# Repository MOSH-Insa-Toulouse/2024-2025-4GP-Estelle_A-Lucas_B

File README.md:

# 2024-2025-4GP-Estelle AUBRY-Lucas BOURDARIE
Projet capteur 2024 - 2025 | Estelle AUBRY et Lucas BOURDARIE | 4ème année, 59ème promotion

# Table des matières

[Présentation du projet](https://github.com/MOSH-Insa-Toulouse/2024-2025-4GP-Haistelle-Lucbourd?tab=readme-ov-file#pr%C3%A9sentation-du-projet)

[I - Un capteur à base de graphite, c'est possible ?](https://github.com/MOSH-Insa-Toulouse/2024-2025-4GP-Haistelle-Lucbourd?tab=readme-ov-file#i---un-capteur-%C3%A0-base-de-graphite-cest-possible-)

[II - Simulation sous LTSpice](https://github.com/MOSH-Insa-Toulouse/2024-2025-4GP-Haistelle-Lucbourd?tab=readme-ov-file#ii---simulation-sous-ltspice)

[III - Réalisation du PCB avec KiCAD](https://github.com/MOSH-Insa-Toulouse/2024-2025-4GP-Haistelle-Lucbourd?tab=readme-ov-file#iii---r%C3%A9alisation-du-pcb-avec-kicad)

[IV - Le banc de test automatisé](https://github.com/MOSH-Insa-Toulouse/2024-2025-4GP-Haistelle-Lucbourd?tab=readme-ov-file#iv---le-banc-de-test-automatis%C3%A9)

[V - Le code Arduino pour piloter le projet](https://github.com/MOSH-Insa-Toulouse/2024-2025-4GP-Haistelle-Lucbourd/tree/main?tab=readme-ov-file#v---le-code-arduino-pour-piloter-le-projet)

[VI - L'application Android avec Mit App Inventor](https://github.com/MOSH-Insa-Toulouse/2024-2025-4GP-Haistelle-Lucbourd/tree/main?tab=readme-ov-file#vi---lapplication-android-avec-mit-app-inventor)

[VII - Résultats](https://github.com/MOSH-Insa-Toulouse/2024-2025-4GP-Haistelle-Lucbourd/tree/main?tab=readme-ov-file#vii---résultats)

# Présentation du projet 
 
<div align="justify"> Ce projet a été mené dans le cadre de l'UF  "Du capteur au banc de test" . L'objectif est de réaliser un capteur de déformation à base de graphite. Pour ce faire, il suffit simplement de déposer du crayon à papier sur un bout de feuille. La tension ou la compression du papier engendre une variation de résistance qui est proportionnelle à la déformation appliquée. Les principes physiques qui se cachent derrière ce phénomène sont expliqués <a href="https://github.com/MOSH-Insa-Toulouse/2024-2025-4GP-Haistelle-Lucbourd/blob/main/README.md#i---un-capteur-%C3%A0-base-de-graphite-cest-possible-">ici</a>. Le projet s'inscrit donc dans une démarche low-tech car le capteur nécessite peu de ressources et sa réalisation est accessible à tous !</div>

<div align="justify"> De plus, le capteur graphite réalisé sera testé de manière à comparer ses performances avec un capteur de déformation commercial. Nous souhaitons dégager les forces et les limites du capteur graphite par rapport à un capteur commercial. Finalement, nous établirons une conclusion quant à la possible industrialisation de ce type de capteur.</div>

<br>

<div style='display:flex' align="center">

 <p><em>Figure 1 : Banc de test complet </em></p>
</div>

<div style='display:flex' align="center">

 <p><em>Figure 2 : Mise en place des deux types de capteurs disponibles </em></p>
</div>

 ## Livrables
À la fin de ce projet, plusieurs livrables sont attendus:
- Un **PCB** sur lequel seront connectés tous les éléments cités dans la partie [Matériel utilisé](https://github.com/MOSH-Insa-Toulouse/2024-2025-4GP-Haistelle-Lucbourd/blob/main/README.md#mat%C3%A9riel-utilis%C3%A9)
- Un **banc de test** pour étudier la déformation du capteur graphite et du capteur commercial
- Un **code Arduino** qui permette de contrôler le banc de test et d'afficher les mesures de résistances
- Une <a href="https://github.com/MOSH-Insa-Toulouse/2024-2025-4GP-Haistelle-Lucbourd/blob/main/LSG180_datasheet.pdf"><strong>datasheet</strong></a> qui énonce toutes les caractéristiques du capteur graphite
- Une **application Android** (.apk) pour visualiser les relevés de mesures en direct

## Matériel utilisé 
Pour le **montage**, voici tout le matériel requis:
- Une carte Arduino UNO
- Un écran OLED (I2C) 
- Un module Bluetooth HC-05
- Un potentiomètre numérique MCP41050
- Un encodeur rotatif
- Un capteur de déformation commercial (FlexSensor) pour effectuer une comparaison
- Un <a href="https://github.com/MOSH-Insa-Toulouse/2024-2025-4GP-Haistelle-Lucbourd/blob/main/Jauge_Contrainte_A_Imprimer.pdf"><strong>capteur de déformation en papier</strong></a>
- Des crayons à papiers différents pour les tests
- Un servo moteur
- Des header de différentes tailles pour fixer les composants sur la PCB
- Une résistance de 33k

Pour réaliser **l'amplificateur transimpédance**, la liste de matériel est la suivante:
- Un amplificateur opérationnel LTC1050
- Deux condensateurs de 100nF
- Un condensateur de 1uF
- Deux résistances de 100k
- Deux résistances de 1k
- Une résistance de 10k

# I - Un capteur à base de graphite, c'est possible ?

<div align="justify">
Oui et c'est ce qu'a montré l'équipe de chercheurs Lin, CW., Zhao, Z., Kim, J. et al. dans l'article <em>Pencil Drawn Strain Gauges and Chemiresistors on Paper</em> paru en 2014. En effet, les crayons à papier sont composés de graphite et d'argile dans des proportions différentes. Par exemple, le crayon HB est constitué à 50% de graphite et à 50% d'argile. Ces différences de compositions entraînent des propriétés de conduction qui diffèrent selon le type de crayon utilisé. Lorsque l'on dépose du crayon à papier sur une feuille, les nanoparticules de graphite déposées constituent un système dit <strong>granulaire</strong>. Il s'agit d'un système dont les grains forment un réseau très désordonné au sein duquel les électrons se déplacent d'un grain à un autre par <strong>effet tunnel</strong>. L'équipe de chercheurs a donc démontré que les crayons <strong>durs</strong> comme l'HB possédaient une résistance plus importante que les crayons <strong>légers</strong> comme le 9B. Ceci s'explique par le fait que les crayons durs comme l'HB contiennent plus d'argile qu'un crayon léger qui contient plus de graphite. L'argile joue le rôle d'un isolant, plus il y en a, plus la conduction des électrons au sein du matériau est difficile. À l'inverse, les nanoparticules de graphite permettent la conduction des électrons, c'est pour cela que le crayon 9B est moins résistif que le crayon HB. 
</div>
 <br>
<div align="center">
  
  <p><em>Figure 3 : Les différents types de crayons: du 9B au 9H</em></p>
 <p><em>d'après le site Passage Clouté à l'adresse<a href="https://passagecloute.com/blog/post/8_comment-choisir-le-bon-crayon-graphite-du-9h-au-9b.html?page_type=post"> suivante</a> </em></p>
</div>
<div align="justify">
De plus, les chercheurs ont aussi prouvé que les crayons pouvaient se comporter comme des <strong>jauges de contraintes</strong>. En dessinant au crayon une forme de U avec deux rectangles au bout pour les électrodes de contact, les chercheurs ont remarqué qu'une déformation en compression et en tension avaient des effets différents sur la <strong>résistance</strong> du capteur. La compression du capteur compresse les particules de graphite et induit une diminution de la résistance. Au contraire, la tension du capteur éloigne les particules de graphite ce qui augmente résistance. 
</div>
<div align="center">
  
  <p><em>Figure 4 : Structure granulaire en compression et en tension</em></p>
</div>

<div align="center">
  
  <p><em>Figure 5 : c) Capteur graphite en compression d) Capteur graphite en tension </em></p>
 <p><em>d'après Lin, CW., Zhao, Z., Kim, J. et al., 2014 </em></p>
</div>

<div align="justify">
Cependant, l'équipe conclut que l'observation de ces phénomènes n'est pas possible pour des crayons composés de plus d'argile que le crayon HB. Selon eux, le réseau de nanoparticules du crayon HB se situe juste au dessus du <strong>seuil de percolation</strong>. Le seuil de percolation est le seuil à partir duquel le matériau devient conducteur car les électrons peuvent traverser. Néanmoins, nous allons montrer que, grâce à l'utilisation d'un <strong>amplificateur transimpédance</strong>, il est possible de mesurer des résistances pour des crayons plus durs que le HB. Par conséquent, la structure de ces crayons permet le passage des électrons et ne se situe pas en dessous du seuil de percolation.   
</div>

# II - Simulation sous LTSpice et formules utiles

<div align="justify"> D'après l'étude menée par les chercheurs, le capteur graphite a une résistance qui peut varier d'une centaine de kohms à quelques Mohms. Les résistances très élevées sont délicates à mesurer. En effet, une méthode classique consiste à utiliser un ohmmètre mais pour mesurer des résistances de cet ordre de grandeur les options sont chères. De plus, nous utilisons une carte Arduino dont l'impédance maximale de la source ne peut pas dépasser 10 kohms. Il n'est donc pas possible de brancher directement notre capteur graphite sur la carte. De ce fait, nous allons amplifier le signal et diminuer son impédance à l'aide d'un amplificateur transimpédance. Nous utilisons pour cela un amplificateur opérationnel LTC1050 car il est suffisamment sensible pour amplifier correctement le signal. Il s'agit également d'un amplificateur très précis, qui possède un offset voltage de 5 uV, négligeable par rapport à la tension mesurée sur l'entrée non-inverseuse. Si l'on considère que le courant délivré par le capteur graphite est de 100 nA et que la résistance de R1 vaut 100komhs, alors la tension Vep = I x R1 = 10 mV >> 5 uV.</div>

## A) Montage avec l'amplificateur transimpédance

<div align="center">
  
  <p><em>Figure 6 : Schéma de l'amplificateur transimpédance dans LTSpice </em></p>
</div>
<div align="justify">
De plus, il va falloir filtrer le bruit. Pour ce faire, nous mettons en place 3 filtres passe-bas:
 <ul>
  <li>un pour filtrer le bruit du capteur en jaune.</li>
  <li>un pour filtrer le bruit à 50Hz en vert.</li>
  <li>un pour filtrer les variations plus rapides que 7kHz en rouge. D'après le critère de Shannon, fech > 2*fsignal. Or, pour une carte Arduino, la fréquence d'échantillonnage vaut 15 kHz donc fsignal < 7kHz.  </li>
</ul>
</div>

## B) Formules
À partir de ce montage, nous pouvons établir la formule nécessaire pour relier la tension en sortie de l'amplificateur transimpédance à la résistance du capteur graphite.

<div align="center">
  
  <p><em>Equation 1 : Formule qui lie la résistance du capteur graphite à la tension Vadc mesurée en sortie </em></p>
</div>

De la même manière, pour le capteur commercial, nous faisons un pont diviseur de tension avec une résistance de 33k. La formule qui relie la tension de sortie à la résistance du capteur commercial est la suivante: 

<div align="center">
  
  <p><em>Equation 2 : Formule qui lie la résistance du capteur commercial à la tension V_flex mesurée en sortie </em></p>
</div>

# III - Réalisation du PCB avec KiCAD

<div align="justify"> Ensuite, nous avons dessiné un PCB simple face à l'aide du logiciel KiCAD. Il est à noter que l'entrée du capteur graphite est reliée à l'amplificateur transimpédance. Afin de permettre un meilleur contrôle de l'amplification du signal, la résistance R2 de la figure 7 a été remplacée par un potentiomètre numérique. Le conditionneur utilisé pour le capteur commercial est un pont diviseur de tension avec une résistance de 33k. De plus, nous avons ajouté un condensateur pour faire du débouncing sur l'encodeur rotatif. Nous avons suivi ces étapes:</div>

**1)** **Dessiner** les composants tels que l'OLED, l'encodeur rotatif, le module Bluetooth, le capteur commercial et le capteur graphite

**2)** Réaliser les **empreintes** de ces composants

**3)** Sélectionner les résistances, les condensateurs et l'AOP pour **réaliser l'amplificateur transimpédance** dans l'éditeur de Schématique

**4)** Établir les **points de connexion** entre la carte Arduino et tous les composants

**5)** **Positionner** les composants sur la PCB

**6)** Importer les **modèles 3D** pour les composants non-présents par défaut dans les librairies (OLED, encoder rotatif, module Bluetooth, capteur commercial)

**7)** Faire **le routage** dans l'éditeur de PCB en évitant au maximum les masses flottantes et les vias

**N.B**: Le servo moteur n'apparaît pas ici car il sera relié à la carte Arduino par le biais d'un header.
<div align="center">
  
  <p><em>Figure 7 : Vue depuis l'éditeur de Schématique </em></p>
</div>

<div align="center">
  
  <p><em>Figure 8 : Vue depuis l'éditeur de PCB </em></p>
</div>

<div align="center">
  
  <p><em>Figure 9 : Vue 3D </em></p>
</div>

# IV - Le banc de test automatisé

<div align="center">
  
  <p><em>Figure 10 : Rendu du banc de test final</em></p>
</div>

<div align="justify"> Afin d'optimiser notre relevé de mesures, nous avons mis au point un banc de test qui courbe automatiquement le capteur de déformation. De cette manière, nous minimisons les risques de dégradation du capteur graphite lors des relevés de mesure car nous ne touchons pas le capteur dès lors qu'il est positionné sur le banc de test. Le banc de test a été réalisé sous Fusion360 puis imprimé en 3D. Ce dernier permet des relevés entièrement personnalisables par l'utilisateur grâce au code Arduino développé. Avec ce banc de test, il est possible de réaliser des mesures sur le capteur graphite et le capteur commercial. Les mesures en tension se sont révélées être plus faciles à mettre en place que les mesures en compression, qui sont plus délicates.</div>

## A) La glissière pilotée par le servo moteur

<div align="center">
  
  <p><em>Figure 11 : Rendu de la glissière écrantée avec encoche fendue ainsi que de l'engrenage fixé au servo</em></p>
</div>

<div align="justify">  Pour courber le capteur de déformation, nous avons utilisé un système de glissière qui se déplace sous l'action du servo moteur. En effet, nous avons conçu un engrenage qui se fixe sur le servo moteur et dont la rotation entraîne une glissière crantée. Le bout de cette glissière est fait en forme d'encoche pour maintenir le capteur. Pour éviter que le capteur sorte de l'encoche au cours des mesures, nous avons également imprimé des petites cales qui assurent le bon positionnement du capteur. Enfin, nous avons imprimé deux glissières différentes, une pour le capteur commercial et une pour le capteur graphite car le capteur commercial est plus long que le capteur graphite. La glissière du capteur commercial possède une petite fente en bas de l'encoche (voir figure 11) pour le maintenir correctement et permettre une déformation qui épouse au mieux les rayons de courbure.</div>

## B) Les rayons de courbure interchangeables
<div style='display:flex' align="center">

 <p><em>Figure 12 : Gamme de rayons de courbure imprimés en 3D</em></p>
</div>

<div align="justify"> Pour tester les capteurs, nous avons imprimé huit supports en 3D avec différents rayons de courbure. Ces supports s'imbriquent sur le banc de test comme nous pouvons le voir sur la figure 11. Les numéros qui figurent sur les supports correspondent à l'angle entre le bord jaune et le bord rouge indiqués sur la figure 12. 
</div>

# V - Le code Arduino pour piloter le projet

## A) Description générale 

<div align="justify"> Le code développé permet à l'utilisateur de gérer facilement et intuitivement le banc de test pour effectuer les mesures. L'affichage se fait sur l'écran OLED sur lequel apparaissent <a href="https://github.com/MOSH-Insa-Toulouse/2024-2025-4GP-Haistelle-Lucbourd/tree/main?tab=readme-ov-file#b-les-diff%C3%A9rentes-fonctionalit%C3%A9s">les différentes fonctionnalités</a>. L'utilisateur peut parcourir les différents menus en tournant l'encoder rotatif dans le sens horaire ou anti-horaire. Pour "rentrer" dans un menu, il suffit d'appuyer sur l'encoder et l'interface se met à jour. Chaque menu possède sa propre fonctionnalité que l'utilisateur peut librement régler. En principe, l'ordre des menus correspond à l'ordre dans lequel l'utilisateur doit effectuer les réglages avant de lancer la mesure via le menu "Démarrage" à la fin. Il est préférable de ne pas placer le capteur sur le banc de test avant le menu "Borne" pour ne pas l'abîmer lors des précédents réglages.</div>

## B) Les différentes fonctionnalités
### 1 - Le menu "BIENVENUE"
<div align="center">
   
 <p><em>Figure 13 : menu de bienvenue </em></p>
</div>
Ce menu souhaite la bienvenue à l'utilisateur. Il ne possède pas de fonctionnalité particulière.

### 2 - Le menu "CONFIGURATION"
<div style='display:flex' align="center">

 <p><em>Figure 14 : menu de configuration </em></p>
</div>
<div align="justify"> Ce menu permet à l'utilisateur de définir quel type de capteur il utilise entre le capteur graphite et le capteur commercial. Une fois le type de capteur sélectionné (fond bleu et écriture noire), il suffit d'appuyer sur l'encoder rotatif pour enregistrer le choix. </div>

### 3 - Le menu "CALIBRATION"
 <div style='display:flex' align="center">

 <p><em>Figure 15 : menu de calibration </em></p>
</div>
<div align="justify"> Dans ce menu, l'utilisateur peut régler la valeur prise par le potentiomètre numérique de manière à ne pas saturer l'amplificateur opérationnel. Attention, ce menu n'est utile que lorsque le type de capteur choisi est le graphite car le potentiomètre numérique est utilisé dans l'amplificateur transimpédance. L'interface affiche à la fois la valeur de résistance prise par le potentiomètre numérique et le signal lu par l'entrée analogique du capteur graphite. Il s'agit donc d'une valeur comprise entre 0 et 1023. Lors des mesures, il faut également anticiper la variation de résistance engendrée par la déformation du capteur graphite. En effet, en compression, la résistance lue diminue donc le signal augmente et peut, si le potentiomètre n'est pas correctement réglé, saturer l'AOP. </div>

### 4 - Le menu "VITESSE"
<div style='display:flex' align="center">

 <p><em>Figure 16 : menu de réglage de la vitesse </em></p>
</div>
<div align="justify"> Dans le menu "Vitesse", l'utilisateur peut régler la vitesse à laquelle il souhaite effectuer les mesures, c'est-à-dire, la vitesse à laquelle la glissière reliée au servo moteur va se déplacer. L'écran affiche un pourcentage qui correspond à la vitesse du servo moteur. 0% correspond à la <strong>vitesse minimale</strong> et 100% la <strong>vitesse maximale</strong>. Pour augmenter la vitesse, il est nécessaire de tourner l'encodeur rotatif dans le sens <strong>anti-horaire</strong> car il s'agit en réalité de <strong>diminuer</strong> le délai entre chaque incrément du servo moteur. La vitesse maximale correspond à un délai de <strong>5ms</strong> tandis que la vitesse minimale correspond à un délai de <strong>40ms</strong>. De plus, lorsque la vitesse change (= l'encodeur change de position), le servo moteur effectue un aller-retour au cours duquel il est possible faire varier la vitesse du servo à l'aide de l'encodeur jusqu'à obtenir la vitesse désirée. L'affichage en % de la vitesse s'effectue <strong> à la fin </strong>  de l'aller-retour. Il n'y a donc pas d'affichage en direct de la vitesse mais seulement après que le servo moteur ait fait un aller-retour. D'après la figure 17 ci-dessous, comme l'encodeur est utilisé pour faire varier le délai, la variable encoder_pos peut prendre des valeurs comprises entre 5 et 40 uniquement. </div>
<div align="center">
  
  <p><em>Figure 17 : Algorigramme qui présente le déroulé de la fonction "Vitesse"</em></p>
</div>

### 5 - Le menu "BORNE"
<div style='display:flex' align="center">

 <p><em>Figure 18 : menu de réglage de la borne </em></p>
</div>
<div align="justify"> À partir de cette étape, il faut placer le capteur sur le banc de test. Le menu "Borne" permet à l'utilisateur de régler la position maximale du servo moteur et par conséquent, celle de l'encoche qui maintient le capteur contre le support. De cette manière, l'utilisateur peut s'assurer que le capteur épouse correctement la forme du rayon de courbure. Pour augmenter ou diminuer la position maximale, il faut tourner l'encodeur rotatif dans le sens horaire ou anti-horaire. </div>
 
### 6 - Le menu "MODE de MESURE"
<div style='display:flex' align="center">

 <p><em>Figure 19 : menu de sélection du mode de mesure </em></p>
</div>
<div align="justify"> À l'intérieur de ce menu, l'utilisateur définit le nombre de mesures qu'il souhaite faire. En effet, nous avons pensé que comme les valeurs de résistances lues en direct peuvent parfois varier, il pourrait être intéressant de permettre à l'utilisateur de faire une moyenne sur un nombre de mesures qu'il définit. De ce fait, lorsque la valeur choisie est "5" par exemple, le code effectuera 5 relevés de résistances pour un même rayon de courbure. Le servo fera donc un aller, une mesure puis un retour, le tout 5 fois. La valeur finale affichée correspondra à une moyenne de la résistance sur les 5 mesures. Le nombre de mesure réalisable est compris entre 1 et 20. </div>

### 7 - Le menu "DÉMARRAGE"
<div style='display:flex' align="center">

 <p><em>Figure 20 : menu de démarrage de la mesure </em></p>
</div>
Le menu "Démarrage" permet de lancer l'acquisition de mesure. Il prend en compte tous les paramètres précédemment définis par l'utilisateur. Par exemple pour des paramètres tels que:
<ul>
<li><strong>Vitesse</strong>: 52%</li>
<li><strong>Borne</strong>: 150</li>
<li><strong>Mode de mesure</strong>: 5</li>
Le servo moteur effectuera 5 aller-retours jusqu'à la position 150 du servo à une vitesse de 52% de la vitesse maximale.
</ul>
<div align="center">
  
  <p><em>Figure 21 : Algorigramme qui présente le déroulé de la fonction "Démarrage"</em></p>
</div>

### 8 - Le menu "LiveVIEW"
<div style='display:flex' align="center">

 <p><em>Figure 22 : menu de mesure en direct </em></p>
</div>
<div align="justify"> Ce menu permet un affichage en direct de la valeur de résistance lue par l'entrée analogique. Il faut se placer à l'intérieur de ce menu pour utiliser l'application Android car les données sont envoyées au téléphone via le module Bluetooth HC-05. </div>

# VI - L'application Android avec Mit App Inventor

<div align="justify"> Cette application permet de recevoir les données envoyées par le module Bluetooth du PCB et de les afficher sous forme de graphique.

[insérer image explicative]

## A) L'écran de démarrage
<div align="justify"> L'écran de démarrage comporte un seul bouton "Démarrer" sur lequel il suffit de cliquer pour lancer l'application.</div>
<br>
<div align="center">
  
  <p><em>Figure 23 : Écran de démarrage de l'application </em></p>
</div>

## B) L'interface principale et ses fonctionnalités

<div align="justify"> Sur le deuxième écran, l'utilisateur doit tout d'abord connecter son téléphone au module Bluetooth pour recevoir les données. Lorsque la connexion est établie, le bouton "Bluetooth connexion" s'affiche en vert. Ensuite, un switch permet de définir quel capteur est utilisé. Si l'on utilise le capteur graphite, il faut renseigner la valeur du potentiomètre numérique dans la case rose pour afficher la bonne valeur de résistance dans la case bleu clair. Par défaut, la valeur de R2 vaut 875 ohms. Un graphique en dessous permet d'afficher en direct les bytes reçus par le module Bluetooth. Les bytes reçus sont également affichés dans la case jaune en dessous du graphique. </div>
<br>
<div align="center">
  
  <p><em>Figure 24 : Écran pour le relevé de mesures en direct </em></p>
</div>

# VII - Résultats

<div align="justify"> 
Pour réaliser nos mesures, nous avons tracé l'évolution de la variation relative de résistance en fonction de la déformation. Pour la variation relative de résistance, nous appliquons la formule ci-dessous. Rplat correspond à la résistance du capteur graphite sans déformation appliquée et Rcourbé à la résistance mesurée quand le capteur est déformé.
<div align="center">
  
  <p><em>Equation 3 : Formule de la variation relative de résistance</em></p>
</div>
Pour calculer la déformation, nous effectuons le calcul ci-dessous pour tous nos rayons de courbure afin de trouver la déformation correspondante. e correspond à l'épaisseur de la feuille de papier utilisée.
 <div align="center">
  
  <p><em>Equation 4: Formule pour calculer la déformation</em></p>
</div>
Le coefficient de proportionnalité qui lie la variation relative de résistance et la déformation correspond à la <strong>sensibilité</strong> du capteur. 
</div>

<div align="justify">  Pour réaliser tous nos tests nous avons choisi une vitesse de 52% pour le servo moteur. Les crayons testés sont le 6B, 5B, 4B, 3B, B, HB, F et H pour des mesures en tension. Les tests ont été effectués sur chaque rayon de courbure disponible. Pour les mesures en compression, les tests ont été réalisés sur les crayons 6B, 3B et HB pour des rayons de courbure allant jusqu'à 24 mm. Pour <strong> chaque point </strong>, nous avons réalisé 5 mesures de résistance pour un type de crayon et un rayon de courbure donné et pris la moyenne de ces 5 mesures comme résultat final. Au total, pour les mesures en tension cela nous fait 8 (crayons) x 8 (supports) x 5 (mesures pour 1 type de crayon et un rayon de courbure donné) = <strong>320 mesures</strong>. Pour les mesures en compression, nous avons 3 (crayons) x 6 (supports) x 5 (mesures) = <strong>90 mesures</strong>. Nous n'avons pas pu réaliser les mesures en compression pour tous les rayons de courbure disponibles car le capteur se détériorait au fur et à mesure des tests.  Ainsi, pour ce projet nous avons effectué plus de <strong>400</strong> mesures pour caractériser nos capteurs. 
</div>

## A) Les mesures obtenues

<div align="justify"> Voici les résultats de toutes nos mesures en tension (figure 25) et en compression (figure 26). Les courbes obtenues sont cohérentes avec les résultats de Lin, CW., Zhao, Z., Kim, J. et al. En effet, les crayons plus durs comme le 6B possèdent une sensibilité plus faible que les crayons plus légers comme le HB par exemple. Voici le graphique qui regroupe nos résultats pour une déformation en tension.   </div>

<div align="center">
  
  <p><em>Figure 25 : Résultats de la déformation du capteur graphite en tension pour différents crayons</em></p>
</div>

Voici le graphique qui regroupe nos résultats pour une déformation en compression.

<div align="center">
  
  <p><em>Figure 26 : Résultats de la déformation du capteur graphite en compression pour différents crayons</em></p>
</div>

Voici quelques courbes individuelles qui permettent d'apprécier l'évolution linéaire de la variation relative de résistance en fonction de la déformation appliquée.

<div align="center">
  
  <p><em>Figure 27 : tension du crayon 3B</em></p>
</div>

<div align="center">
  
  <p><em>Figure 28 : tension du crayon HB </em></p>
</div>

<div align="center">
  
  <p><em>Figure 29 : tension du crayon H </em></p>
</div>

<div align="center">
  
  <p><em>Figure 30 : compression du crayon 3B </em></p>
</div>

<div align="center">
  
  <p><em>Figure 31 : compression du crayon HB </em></p>
</div>

Nous avons également réalisé nos tests sur le capteur commercial pour pouvoir effectuer une comparaison.

<div align="center">
  
  <p><em>Figure 32 : tension du capteur commercial </em></p>
</div>

Voici un tableau récapitulatif de nos relevés de mesures.

<div align="center">
  
  <p><em>Figure 33 : Sensibilité des capteurs testés </em></p>
</div>

## B) Comparaison avec un capteur commercial: qui sera le meilleur ?
<div align="justify">   Grâce aux résultats ci-dessus, nous pouvons comparer les performances du capteur graphite par rapport au capteur commercial. Ce sont deux capteurs différents qui ont chacun leur propre domaine d'utilisation. Voici les points positifs et négatifs du capteur commercial.
</div>
<br>
 
<div align="center">
<table>
  <thead>
    <tr>
      <th>Points positifs</th>
      <th>Points négatifs</th>
    </tr>
  </thead>
  <tbody>
    <tr>
      <td>Précision importante</td>
      <td>Impossible de faire une mesure en compression</td>
    </tr>
    <tr>
      <td>Sensibilité élevée</td>
      <td>Coûte beaucoup plus cher qu'un capteur graphite (10 euros environ)</td>
    </tr>
   <tr>
      <td>Réutilisable un grand nombre de fois sans détérioration</td>
      <td></td>
    </tr>
  </tbody>
</table>
</div>
 
 De même, voici un tableau qui récapitule les avantages et inconvénients du capteur graphite.
 
 <div align="center">
<table>
  <thead>
    <tr>
      <th>Points positifs</th>
      <th>Points négatifs</th>
    </tr>
  </thead>
  <tbody>
    <tr>
      <td>Sensibilité qui peut rivaliser avec celle du capteur commercial selon le type de crayon utilisé</td>
      <td>Manipulation délicate car le capteur se détériore au moindre contact</td>
    </tr>
    <tr>
      <td>Permet de réaliser des mesures en compression</td>
      <td>Si le capteur est courbé trop de fois les fibres du papiers se cassent ce qui nuit à la mesure</td>
    </tr>
  </tbody>
</table>
</div>

<div align="justify"> Pour conclure, le capteur graphite a une gamme d'utilisation plus large que le capteur commercial. Sa sensibilité peut égaler celle du capteur commercial. Il reste cependant très délicat et contraignant à manipuler. Nous pensons qu'une piste d'amélioration possible pour ce capteur serait d'envisager un moyen de l'encapsuler pour protéger le graphite. Avec une telle solution, il serait possible de l'industrialiser pour le rendre plus durable. Toutefois, la solution ne devra pas être trop coûteuse pour ne pas perdre l'intérêt de ce capteur qui se veut low-tech avant tout.
</div>

# Contacts

Estelle AUBRY:<a> eaubry@insa-toulouse.fr</a>

Lucas BOURDARIE:<a> bourdari@insa-toulouse.fr</a>

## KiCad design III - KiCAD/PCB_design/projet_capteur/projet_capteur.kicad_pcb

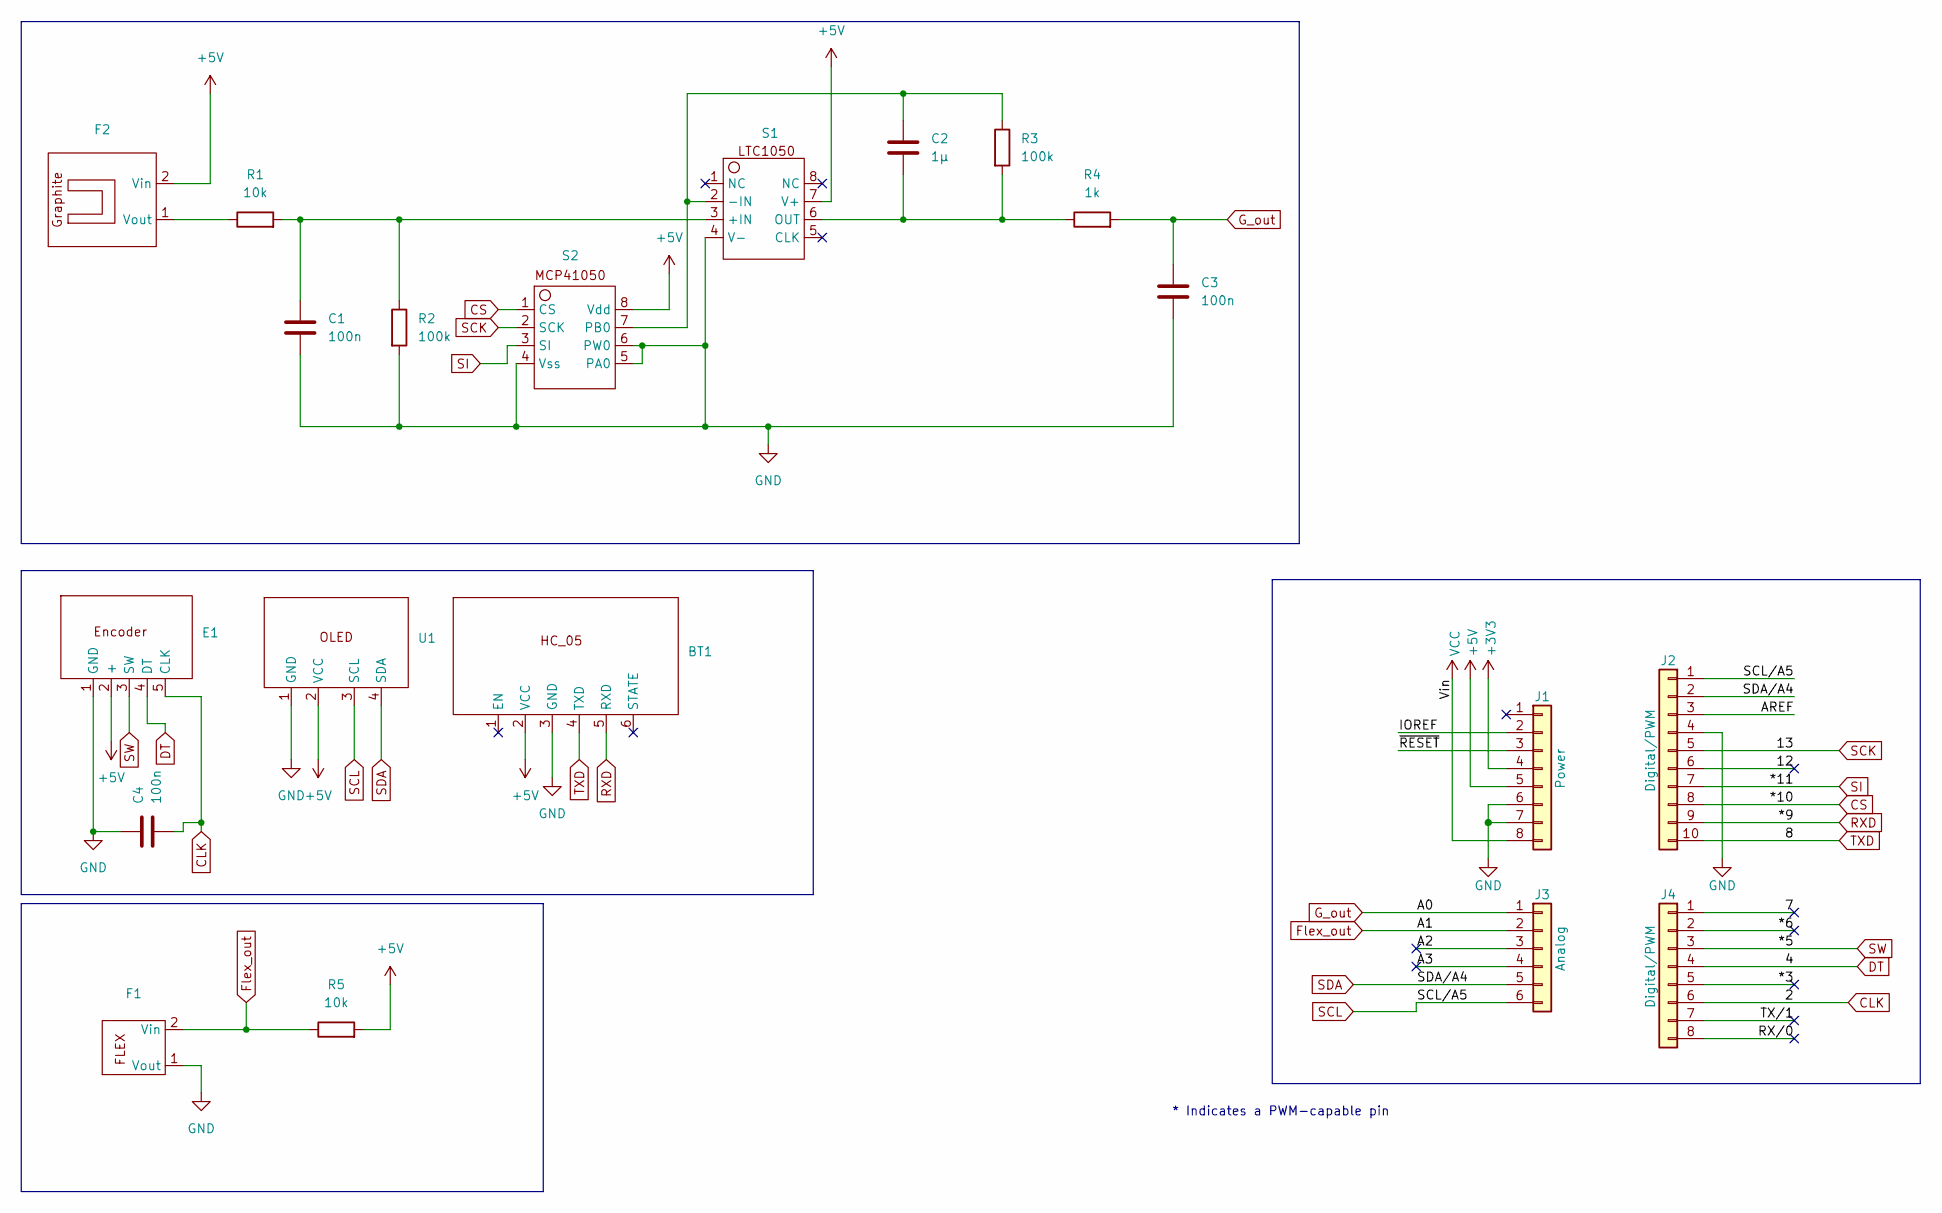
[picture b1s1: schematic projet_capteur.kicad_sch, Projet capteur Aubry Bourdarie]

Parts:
BT1: SIP-6
C1, C3, C4: 100n; C_Disc_D4.3mm_W1.9mm_P5.00mm
C2: 1µ; C_Rect_L7.0mm_W4.5mm_P5.00mm
E1: Encoder
F1, F2: Flex_sens
J1: Power; PinSocket_1x08_P2.54mm_Vertical
J2: Digital/PWM; PinSocket_1x10_P2.54mm_Vertical
J3: Analog; PinSocket_1x06_P2.54mm_Vertical
J4: Digital/PWM; PinSocket_1x08_P2.54mm_Vertical
R1, R5: 10k; Resistance
R2, R3: 100k; Resistance
R4: 1k; Resistance
S1, S2: Support_ampli
U1: SIP-4

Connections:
+3V3: J1.4
+5V: BT1.2 (VCC), E1.2 (+), F2.2 (Vin), J1.5, R5.2, S1.7 (V+), S2.8 (Vdd), U1.2 (VCC)
/7: J4.1
/12: J2.6
/*3: J4.5
/*6: J4.2
/A2: J3.3
/A3: J3.4
/AREF: J2.3
/IOREF: J1.2
/RX/0: J4.8
/TX/1: J4.7
/~RESET: J1.3
CLK: C4.2, E1.5 (CLK), J4.6
CS: J2.8, S2.1 (CS)
DT: E1.4 (DT), J4.4
Flex_out: F1.2 (Vin), J3.2, R5.1
GND: BT1.3 (GND), C1.2, C3.2, C4.1, E1.1 (GND), F1.1 (Vout), J1.6, J1.7, J2.4, R2.2, S1.4 (V-), S2.4 (Vss), S2.5 (PA0), S2.6 (PW0), U1.1 (GND)
G_out: C3.1, J3.1, R4.2
unnamed: F2.1 (Vout), R1.1
unnamed: C1.1, R1.2, R2.1, S1.3 (+IN)
unnamed: C2.1, R3.1, S1.2 (-IN), S2.7 (PB0)
unnamed: C2.2, R3.2, R4.1, S1.6 (OUT)
RXD: BT1.5 (RXD), J2.9
SCK: J2.5, S2.2 (SCK)
SCL: J2.1, J3.6, U1.3 (SCL)
SDA: J2.2, J3.5, U1.4 (SDA)
SI: J2.7, S2.3 (SI)
SW: E1.3 (SW), J4.3
TXD: BT1.4 (TXD), J2.10
VCC: J1.8

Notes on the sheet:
* Indicates a PWM-capable pin

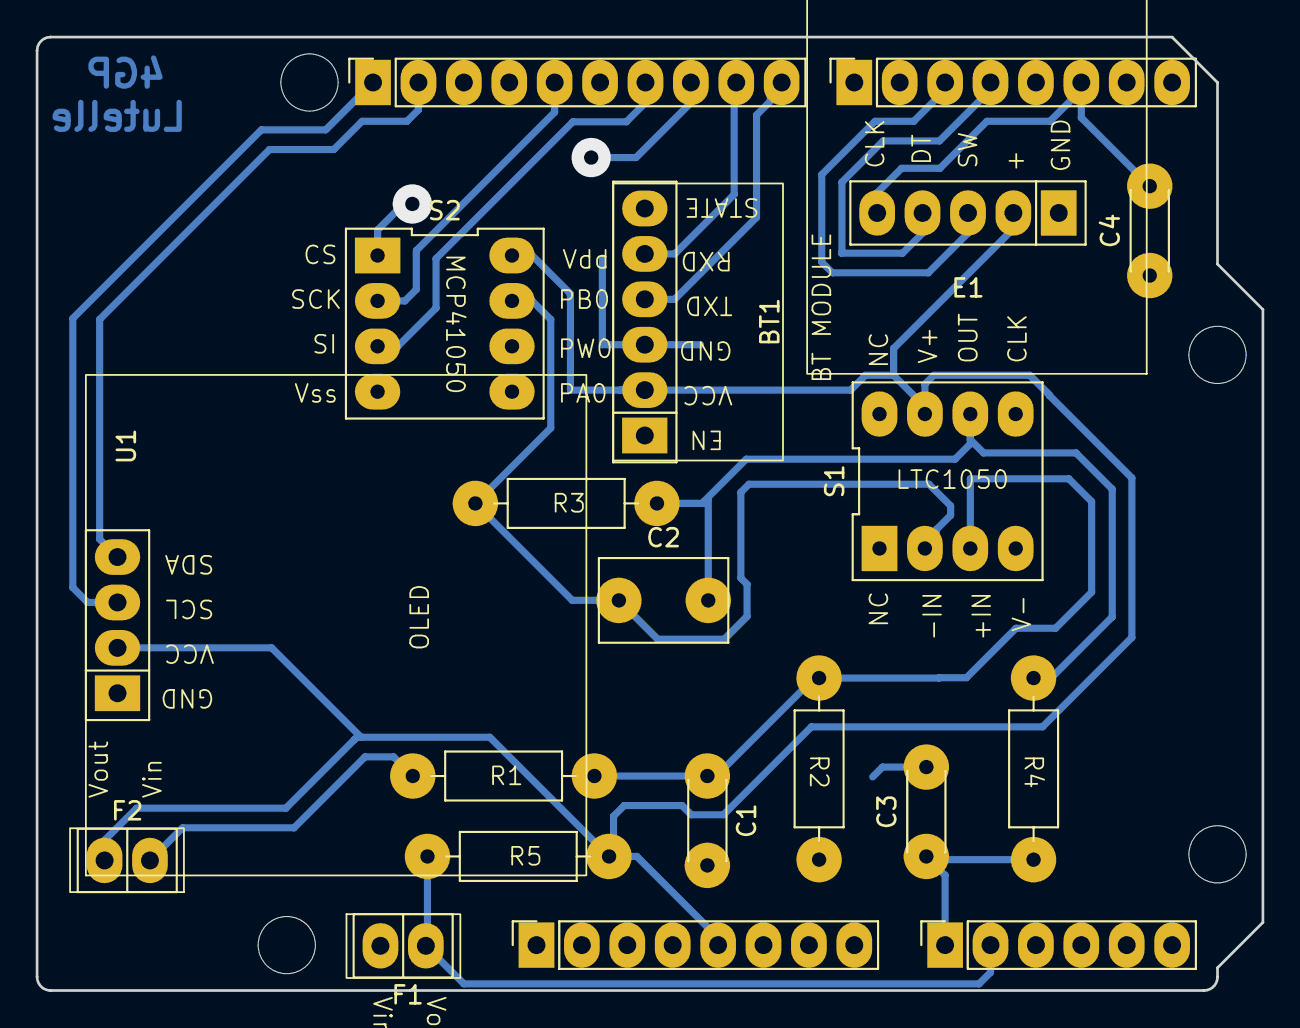
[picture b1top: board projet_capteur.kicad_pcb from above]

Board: 2 copper layers, 68.6 x 53.3 mm, 24 parts (0 on the bottom side), 18 nets.

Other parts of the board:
MH1, MH2, MH3, MH4: MountingHole_3.2mm

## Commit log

2025-04-16 Create I-Photos
2025-04-16 Create test
2025-04-16 Upload files
2025-04-16 VI - Application Android/test
2025-04-17 Dossier renomme
2025-04-18 Rename Bienvenu.jpg to Bienvenue.jpg
2025-04-20 Changement de nom
2025-04-21 Rename Rayons_courbures.JPG to Rayons_courbure.JPG
2025-05-20 Create PCB_design
